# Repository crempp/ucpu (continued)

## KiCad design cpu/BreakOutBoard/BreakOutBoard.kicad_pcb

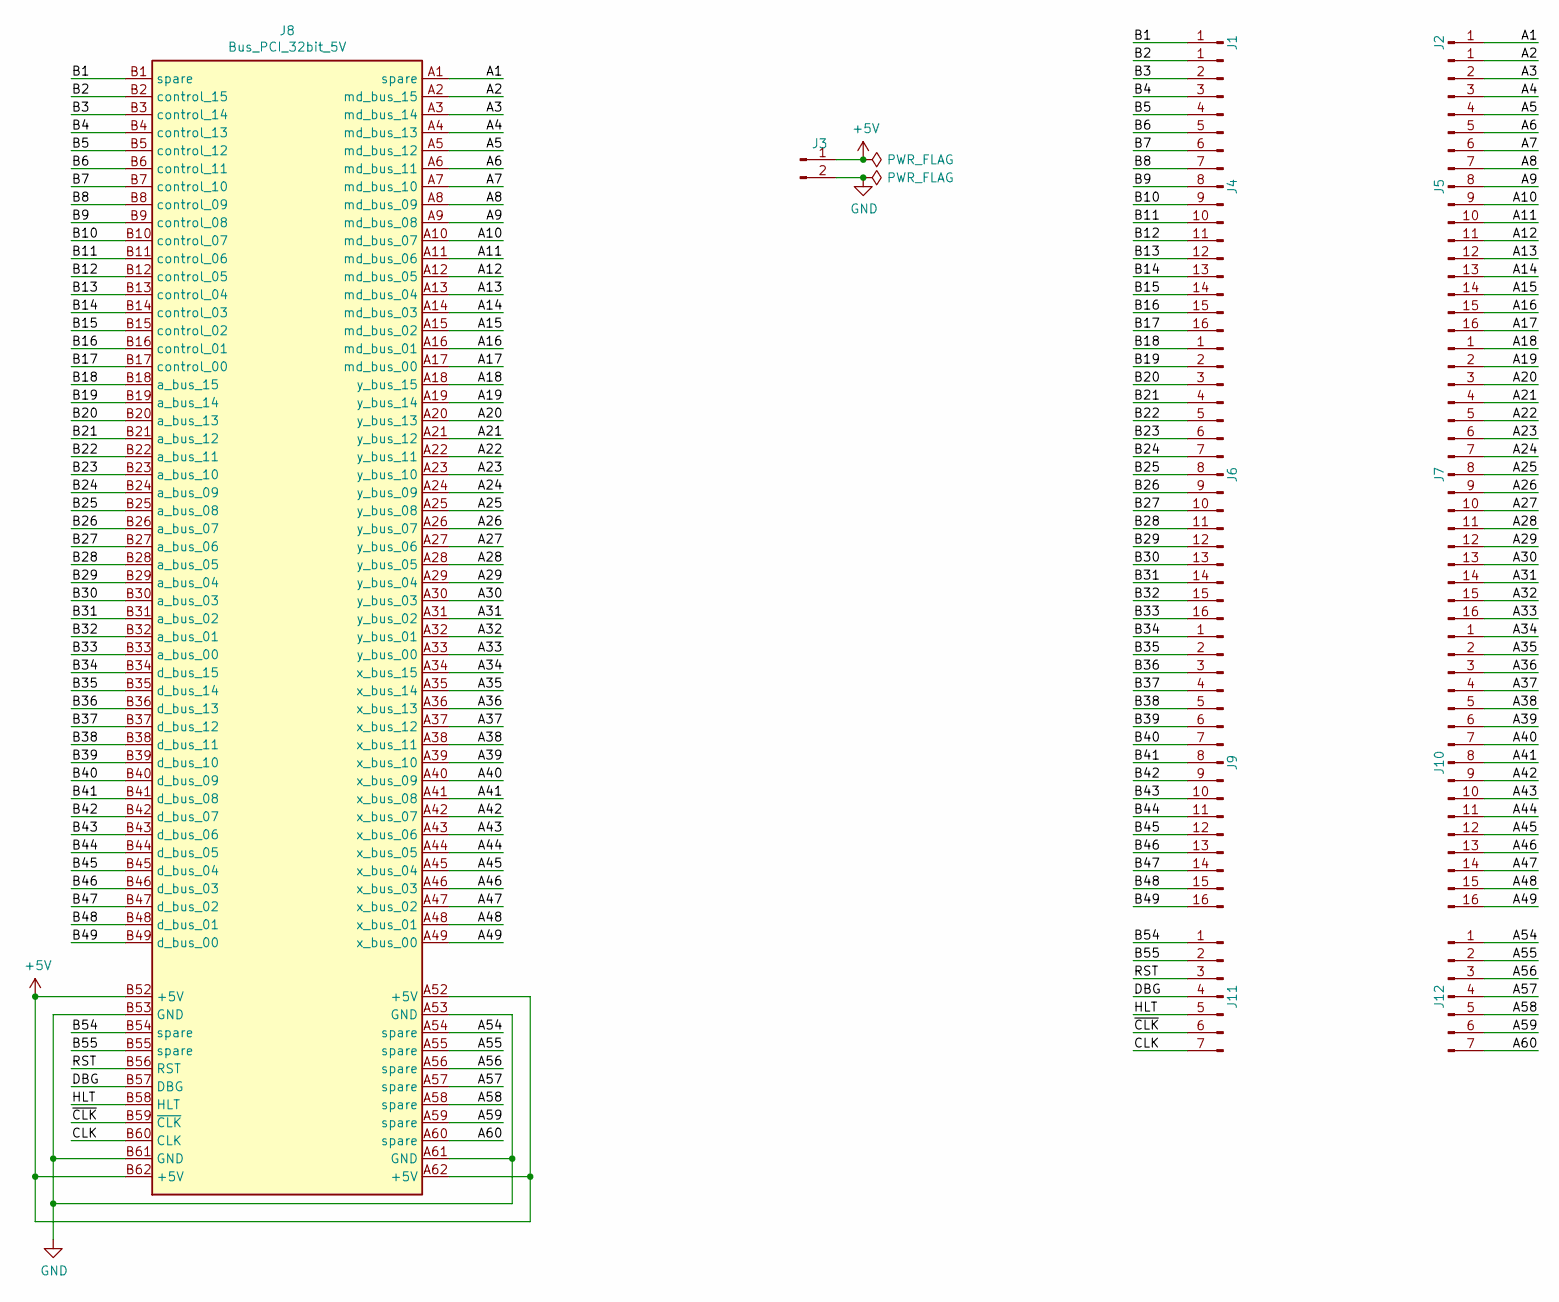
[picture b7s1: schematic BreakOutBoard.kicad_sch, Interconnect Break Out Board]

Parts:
J1, J2: Conn_01x01_Male; PinHeader_1x01_P2.54mm_Vertical
J3: Conn_01x02_Male; PinHeader_1x02_P2.54mm_Vertical
J4, J5, J6, J7, J9, J10: Conn_01x16_Male; PinHeader_1x16_P2.54mm_Vertical
J8: Bus_PCI_32bit_5V; TE_1-5145154-2
J11, J12: Conn_01x07_Male; PinHeader_1x07_P2.54mm_Vertical

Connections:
+5V: J3.1, J8.A52 (+5V), J8.A62 (+5V), J8.B52 (+5V), J8.B62 (+5V)
/A1: J2.1, J8.A1 (spare)
/A2: J5.1, J8.A2 (md_bus_15)
/A3: J5.2, J8.A3 (md_bus_14)
/A4: J5.3, J8.A4 (md_bus_13)
/A5: J5.4, J8.A5 (md_bus_12)
/A6: J5.5, J8.A6 (md_bus_11)
/A7: J5.6, J8.A7 (md_bus_10)
/A8: J5.7, J8.A8 (md_bus_09)
/A9: J5.8, J8.A9 (md_bus_08)
/A10: J5.9, J8.A10 (md_bus_07)
/A11: J5.10, J8.A11 (md_bus_06)
/A12: J5.11, J8.A12 (md_bus_05)
/A13: J5.12, J8.A13 (md_bus_04)
/A14: J5.13, J8.A14 (md_bus_03)
/A15: J5.14, J8.A15 (md_bus_02)
/A16: J5.15, J8.A16 (md_bus_01)
/A17: J5.16, J8.A17 (md_bus_00)
/A18: J7.1, J8.A18 (y_bus_15)
/A19: J7.2, J8.A19 (y_bus_14)
/A20: J7.3, J8.A20 (y_bus_13)
/A21: J7.4, J8.A21 (y_bus_12)
/A22: J7.5, J8.A22 (y_bus_11)
/A23: J7.6, J8.A23 (y_bus_10)
/A24: J7.7, J8.A24 (y_bus_09)
/A25: J7.8, J8.A25 (y_bus_08)
/A26: J7.9, J8.A26 (y_bus_07)
/A27: J7.10, J8.A27 (y_bus_06)
/A28: J7.11, J8.A28 (y_bus_05)
/A29: J7.12, J8.A29 (y_bus_04)
/A30: J7.13, J8.A30 (y_bus_03)
/A31: J7.14, J8.A31 (y_bus_02)
/A32: J7.15, J8.A32 (y_bus_01)
/A33: J7.16, J8.A33 (y_bus_00)
/A34: J8.A34 (x_bus_15), J10.1
/A35: J8.A35 (x_bus_14), J10.2
/A36: J8.A36 (x_bus_13), J10.3
/A37: J8.A37 (x_bus_12), J10.4
/A38: J8.A38 (x_bus_11), J10.5
/A39: J8.A39 (x_bus_10), J10.6
/A40: J8.A40 (x_bus_09), J10.7
/A41: J8.A41 (x_bus_08), J10.8
/A42: J8.A42 (x_bus_07), J10.9
/A43: J8.A43 (x_bus_06), J10.10
/A44: J8.A44 (x_bus_05), J10.11
/A45: J8.A45 (x_bus_04), J10.12
/A46: J8.A46 (x_bus_03), J10.13
/A47: J8.A47 (x_bus_02), J10.14
/A48: J8.A48 (x_bus_01), J10.15
/A49: J8.A49 (x_bus_00), J10.16
/A54: J8.A54 (spare), J12.1
/A55: J8.A55 (spare), J12.2
/A56: J8.A56 (spare), J12.3
/A57: J8.A57 (spare), J12.4
/A58: J8.A58 (spare), J12.5
/A59: J8.A59 (spare), J12.6
/A60: J8.A60 (spare), J12.7
/B1: J1.1, J8.B1 (spare)
/B2: J4.1, J8.B2 (control_15)
/B3: J4.2, J8.B3 (control_14)
/B4: J4.3, J8.B4 (control_13)
/B5: J4.4, J8.B5 (control_12)
/B6: J4.5, J8.B6 (control_11)
/B7: J4.6, J8.B7 (control_10)
/B8: J4.7, J8.B8 (control_09)
/B9: J4.8, J8.B9 (control_08)
/B10: J4.9, J8.B10 (control_07)
/B11: J4.10, J8.B11 (control_06)
/B12: J4.11, J8.B12 (control_05)
/B13: J4.12, J8.B13 (control_04)
/B14: J4.13, J8.B14 (control_03)
/B15: J4.14, J8.B15 (control_02)
/B16: J4.15, J8.B16 (control_01)
/B17: J4.16, J8.B17 (control_00)
/B18: J6.1, J8.B18 (a_bus_15)
/B19: J6.2, J8.B19 (a_bus_14)
/B20: J6.3, J8.B20 (a_bus_13)
/B21: J6.4, J8.B21 (a_bus_12)
/B22: J6.5, J8.B22 (a_bus_11)
/B23: J6.6, J8.B23 (a_bus_10)
/B24: J6.7, J8.B24 (a_bus_09)
/B25: J6.8, J8.B25 (a_bus_08)
/B26: J6.9, J8.B26 (a_bus_07)
/B27: J6.10, J8.B27 (a_bus_06)
/B28: J6.11, J8.B28 (a_bus_05)
/B29: J6.12, J8.B29 (a_bus_04)
/B30: J6.13, J8.B30 (a_bus_03)
/B31: J6.14, J8.B31 (a_bus_02)
/B32: J6.15, J8.B32 (a_bus_01)
/B33: J6.16, J8.B33 (a_bus_00)
/B34: J8.B34 (d_bus_15), J9.1
/B35: J8.B35 (d_bus_14), J9.2
/B36: J8.B36 (d_bus_13), J9.3
/B37: J8.B37 (d_bus_12), J9.4
/B38: J8.B38 (d_bus_11), J9.5
/B39: J8.B39 (d_bus_10), J9.6
/B40: J8.B40 (d_bus_09), J9.7
/B41: J8.B41 (d_bus_08), J9.8
/B42: J8.B42 (d_bus_07), J9.9
/B43: J8.B43 (d_bus_06), J9.10
/B44: J8.B44 (d_bus_05), J9.11
/B45: J8.B45 (d_bus_04), J9.12
/B46: J8.B46 (d_bus_03), J9.13
/B47: J8.B47 (d_bus_02), J9.14
/B48: J8.B48 (d_bus_01), J9.15
/B49: J8.B49 (d_bus_00), J9.16
/B54: J8.B54 (spare), J11.1
/B55: J8.B55 (spare), J11.2
/CLK: J8.B60 (CLK), J11.7
/DBG: J8.B57 (DBG), J11.4
/HLT: J8.B58 (HLT), J11.5
/RST: J8.B56 (RST), J11.3
/~CLK: J8.B59 (~CLK), J11.6
GND: J3.2, J8.A53 (GND), J8.A61 (GND), J8.B53 (GND), J8.B61 (GND)

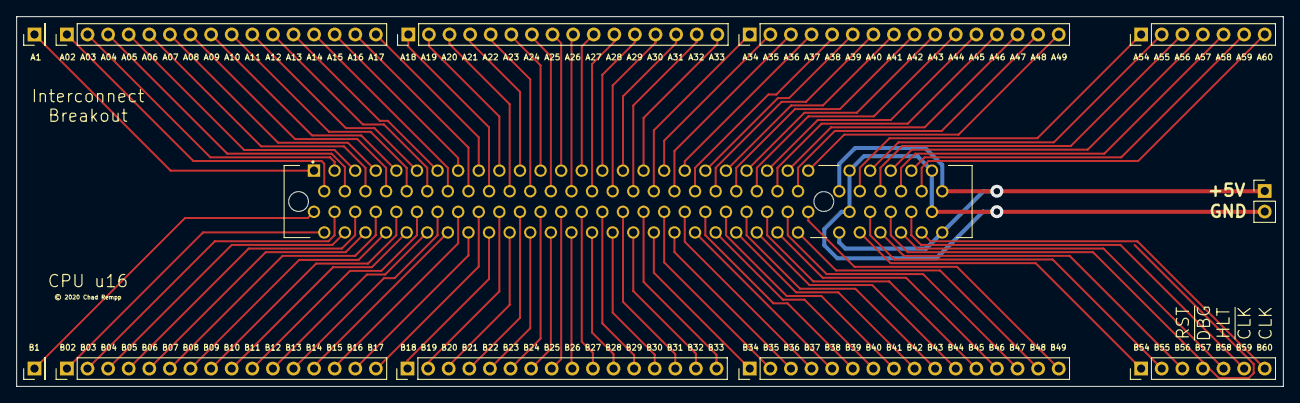
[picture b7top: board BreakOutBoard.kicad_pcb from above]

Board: 2 copper layers, 156.2 x 45.6 mm, 12 parts (0 on the bottom side), 114 nets.

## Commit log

2020-04-23 Initial Commit: GPR and timer v1 complete
2020-06-23 Lots of changes
2020-07-16 Completed initial version of ALU. Created blank memory schematic.
2020-07-17 Part 1 of Bus Control (DBUS read/write)
2020-08-17 ALU and constant register first version
2020-08-24 Update ALU schematic with D_BUS connection, added test points.
2020-08-24 Working on ALU PCB
2020-08-28 Finished a draft of the ALU PCB
2020-11-28 Completed GPR 1.2 PCB and started lots of other things. * Started ALU * Updated Constant Reg * Completed v1.2 GPR * Added random symbols * Updated Memory * Updated plots
2020-11-28 Added missing power pins to GPR
2020-11-28 Added 10uF caps to GPR
2020-12-01 Interconnect Breakout Board
2020-12-01 GPR final production version 1.2
2020-12-01 Readme
2020-12-01 More README
2020-12-26 Fixed errors on GPR after testing board. * writing too small * stat LEDs not aligned * stat buffer needed CE to be active low - swapped 126 for a 125 * x_bus was backwards on the interconnect
2020-12-29 Pipeline ROM builder and architecture representation
2020-12-29 First draft of compiler
2021-01-16 V1.3 of GPR (fixed issues from first production board)
2021-01-24 Finished Address Register 1.0
2022-01-11 Finishing touches on GPR and Address Register
2022-01-30 Upgrade to KiCad 6 and commit a bunch of random stuff
2022-02-05 Moved documentation to Hugo
2022-02-05 deploy: 3e6cc20c77c9a8346d52ee3fa546ec0181f31dfd
2022-02-05 deploy: 4daf2911494d7995c4a63246f400cdf3d3dc522b
2022-02-05 deploy: 7e3fac5a0c15a59fd68d64dcf9501daf894baed8
2022-02-05 deploy: ab9cdf8bbd6255af6afea2acc009ba1ee6c1e917
2022-02-05 deploy: c237bdade34c5e5ddbf67da6ff2dc9f3c88ce5b3
2022-02-05 Fix github pages action 9 (+8 squashed commits) Squashed commits: [ab9cdf8] Fix github pages action 8 [7e3fac5] Fix github pages action 7 [4daf291] Fix github pages action 6 [3e6cc20] Fix github page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
2022-02-05 deploy: e5f184a5c1456ef52129f9dde5b622d77a857407
2022-02-07 New doc theme, more docs
2022-02-07 deploy: f4604b4079bc697abfb9d97187d2978317d579b4
2022-02-09 Memory module v2.0 schematic
2022-02-12 Started memory pcb layout
2022-02-12 deploy: c5714b686755c8e5ee4830019f9f3bb97917d5bf
2022-02-12 Removed and ignored cpu-backups
2022-02-14 Finished a draft of mem pcb
2022-02-20 More doc updates
2022-02-20 Mem module fixes
2022-02-20 deploy: 70283c67c0607eb02cc70333cb4b286954355f9f
2022-02-22 Wrote Arduino tests for Address Register
2022-02-22 Made some changes to the Address register
2022-02-22 GPR v1.4, removed old src, deleted a BOM
2022-02-26 Added gitattributes
2022-02-26 Address Register v1.3
2022-02-26 GPR 1.4, smaller traces and fixed connections being backwards
2022-02-26 Started mini backplane
2022-02-26 Started gocc assembler
